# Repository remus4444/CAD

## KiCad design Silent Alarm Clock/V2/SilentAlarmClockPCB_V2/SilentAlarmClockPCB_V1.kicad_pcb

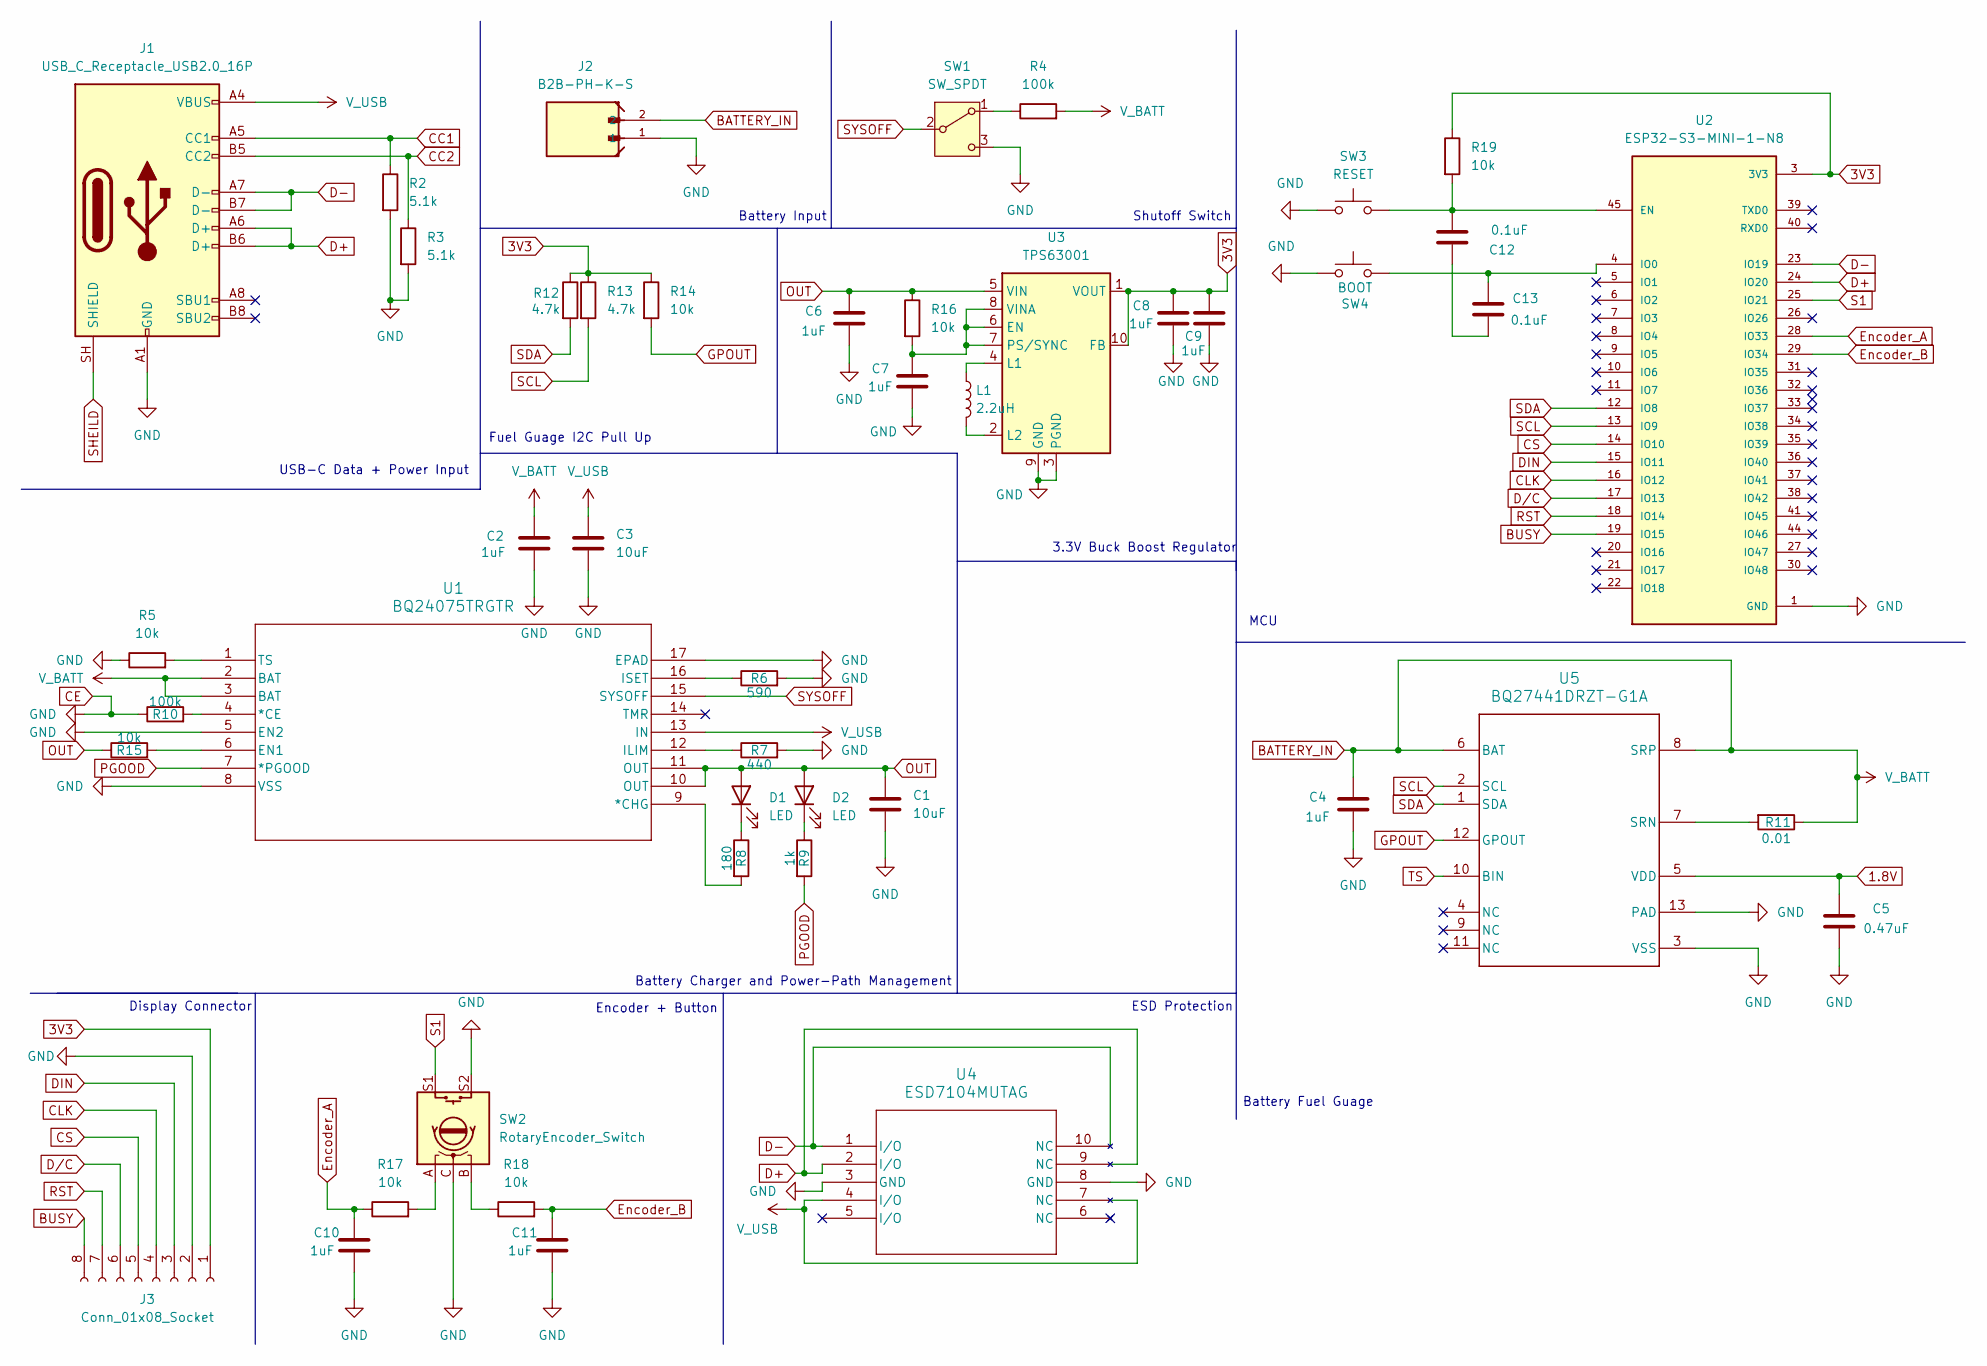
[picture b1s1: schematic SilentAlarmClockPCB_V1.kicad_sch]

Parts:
C1, C3: 10uF; C_0603_1608Metric
C2, C4, C6, C7, C8, C9, C10, C11: 1uF; C_0603_1608Metric
C5: 0.47uF; C_0603_1608Metric
C12, C13: 0.1uF; C_0603_1608Metric
D1: LED; LED_0603_1608Metric_Pad1.05x0.95mm_HandSolder
D2: LED; LED_0603_1608Metric
J1: USB_C_Receptacle_USB2.0_16P; USB_C_Receptacle_GCT_USB4105-xx-A_16P_TopMnt_Horizontal
J2: B2B-PH-K-S; JST_B2B-PH-K-S
J3: Conn_01x08_Socket; JST_PH_B8B-PH-K_1x08_P2.00mm_Vertical
L1: 2.2uH; L_1008_2520Metric
R2, R3: 5.1k; R_0603_1608Metric
R4, R10: 100k; R_0603_1608Metric
R5, R14, R15, R16, R17, R18, R19: 10k; R_0603_1608Metric
R6: 590; R_0603_1608Metric
R7: 440; R_0603_1608Metric
R8: 180; R_0603_1608Metric
R9: 1k; R_0603_1608Metric
R11: 0.01; R_0603_1608Metric
R12, R13: 4.7k; R_0603_1608Metric
SW1: SW_SPDT; SW_SPDT_CK_JS102011SAQN
SW2: RotaryEncoder_Switch; XDCR_PEC11R-4220F-S0024
SW3: RESET; SW_SPST_PTS810
SW4: BOOT; SW_SPST_PTS810
U1: BQ24075TRGTR; RGT16_1P7X1P7
U2: ESP32-S3-MINI-1-N8; XCVR_ESP32-S3-MINI-1-N8; PARTREV v0.6
U3: TPS63001; Texas_DRC0010J_ThermalVias
U4: ESD7104MUTAG; UDFN10_ONS
U5: BQ27441DRZT-G1A; Copy of DRZ0012A

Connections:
1.8V: C5.2, U5.5 (VDD)
3V3: C8.2, C9.2, J3.1, R12.1, R13.1, R14.1, R19.1, U2.3 (3V3), U3.1 (VOUT), U3.10 (FB)
BATTERY_IN: C2.1, C4.2, J2.2, R4.2, R11.1, U1.2 (BAT), U1.3 (BAT), U5.6 (BAT), U5.8 (SRP)
BUSY: J3.8, U2.19 (IO15)
CC1: J1.A5 (CC1), R2.1
CC2: J1.B5 (CC2), R3.1
CLK: J3.4, U2.16 (IO12)
CS: J3.5, U2.14 (IO10)
D+: J1.A6 (D+), J1.B6 (D+), U2.24 (IO20), U4.2 (I/O), U4.9 (NC)
D-: J1.A7 (D-), J1.B7 (D-), U2.23 (IO19), U4.1 (I/O), U4.10 (NC)
DIN: J3.3, U2.15 (IO11)
D/C: J3.6, U2.17 (IO13)
Encoder_A: C10.2, R17.1, U2.28 (IO33)
Encoder_B: C11.2, R18.2, U2.29 (IO34)
GND: C1.2, C2.2, C3.2, C4.1, C5.1, C6.1, C7.1, C8.1, C9.1, C10.1, C11.1, J1.A1 (GND), J1.A12 (GND), J1.B1 (GND), J1.B12 (GND), J2.1, J3.2, R2.2, R3.2, R5.1, R6.2, R7.2, R10.1, SW1.3 (C), SW2.C, SW2.S2, SW3.1, SW4.1, U1.5 (EN2), U1.8 (VSS), U1.17 (EPAD), U2.1 (GND), U2.2 (GND), U2.42 (GND), U2.43 (GND), U2.46 (GND), U2.47 (GND), U2.48 (GND), U2.49 (GND), U2.50 (GND), U2.51 (GND), U2.52 (GND), U2.53 (GND), U2.54 (GND), U2.55 (GND), U2.56 (GND), U2.57 (GND), U2.58 (GND), U2.59 (GND), U2.60 (GND), U2.61 (GND), U2.61_1 (GND), U2.61_2 (GND), U2.61_3 (GND), U2.61_4 (GND), U2.61_5 (GND), U2.61_6 (GND), U2.61_7 (GND), U2.61_8 (GND), U2.62 (GND), U2.63 (GND), U2.64 (GND), U2.65 (GND), U3.3 (PGND), U3.9 (GND), U3.11 (PGND), U4.3 (GND), U4.8 (GND), U5.3 (VSS), U5.13 (PAD), U5.V; also elsewhere on the board
GPOUT: R14.2, U5.12 (GPOUT)
unnamed: C12.1, C13.1
unnamed: D1.1 (K), R8.1
unnamed: D2.1 (K), R9.1
unnamed: R17.2, SW2.A
unnamed: R18.1, SW2.B
unnamed: R4.1, SW1.1 (A)
unnamed: R10.2, U1.4 (*CE)
unnamed: R8.2, U1.9 (*CHG)
unnamed: R15.2, U1.6 (EN1)
unnamed: R7.1, U1.12 (ILIM)
unnamed: R6.1, U1.16 (ISET)
unnamed: R5.2, U1.1 (TS)
unnamed 28: C12.2, R19.2, SW3.2, U2.45 (EN); also elsewhere on the board
unnamed 29: C13.2, SW4.2, U2.4 (IO0); also elsewhere on the board
unnamed: C7.2, R16.2, U3.6 (EN), U3.7 (PS/SYNC), U3.8 (VINA)
unnamed: L1.1, U3.4 (L1)
unnamed: L1.2, U3.2 (L2)
unnamed: R11.2, U5.7 (SRN)
OUT: C1.1, C6.2, D1.2 (A), D2.2 (A), R15.1, R16.1, U1.10 (OUT), U1.11 (OUT), U3.5 (VIN)
PGOOD: R9.2, U1.7 (*PGOOD)
RST: J3.7, U2.18 (IO14)
S1: SW2.S1, U2.25 (IO21)
SCL: R13.2, U2.13 (IO9), U5.2 (SCL)
SDA: R12.2, U2.12 (IO8), U5.1 (SDA)
SHEILD: J1.SH (SHIELD)
SYSOFF: SW1.2 (B), U1.15 (SYSOFF)
TS: U5.10 (BIN)
V_USB: C3.1, J1.A4 (VBUS), J1.A9 (VBUS), J1.B4 (VBUS), J1.B9 (VBUS), U1.13 (IN), U4.4 (I/O), U4.7 (NC)

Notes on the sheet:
Battery Input
MCU
Battery Fuel Guage
Battery Charger and Power-Path Management
3.3V Buck Boost Regulator
Display Connector
ESD Protection
Shutoff Switch
Fuel Guage I2C Pull Up
Encoder + Button
USB-C Data + Power Input

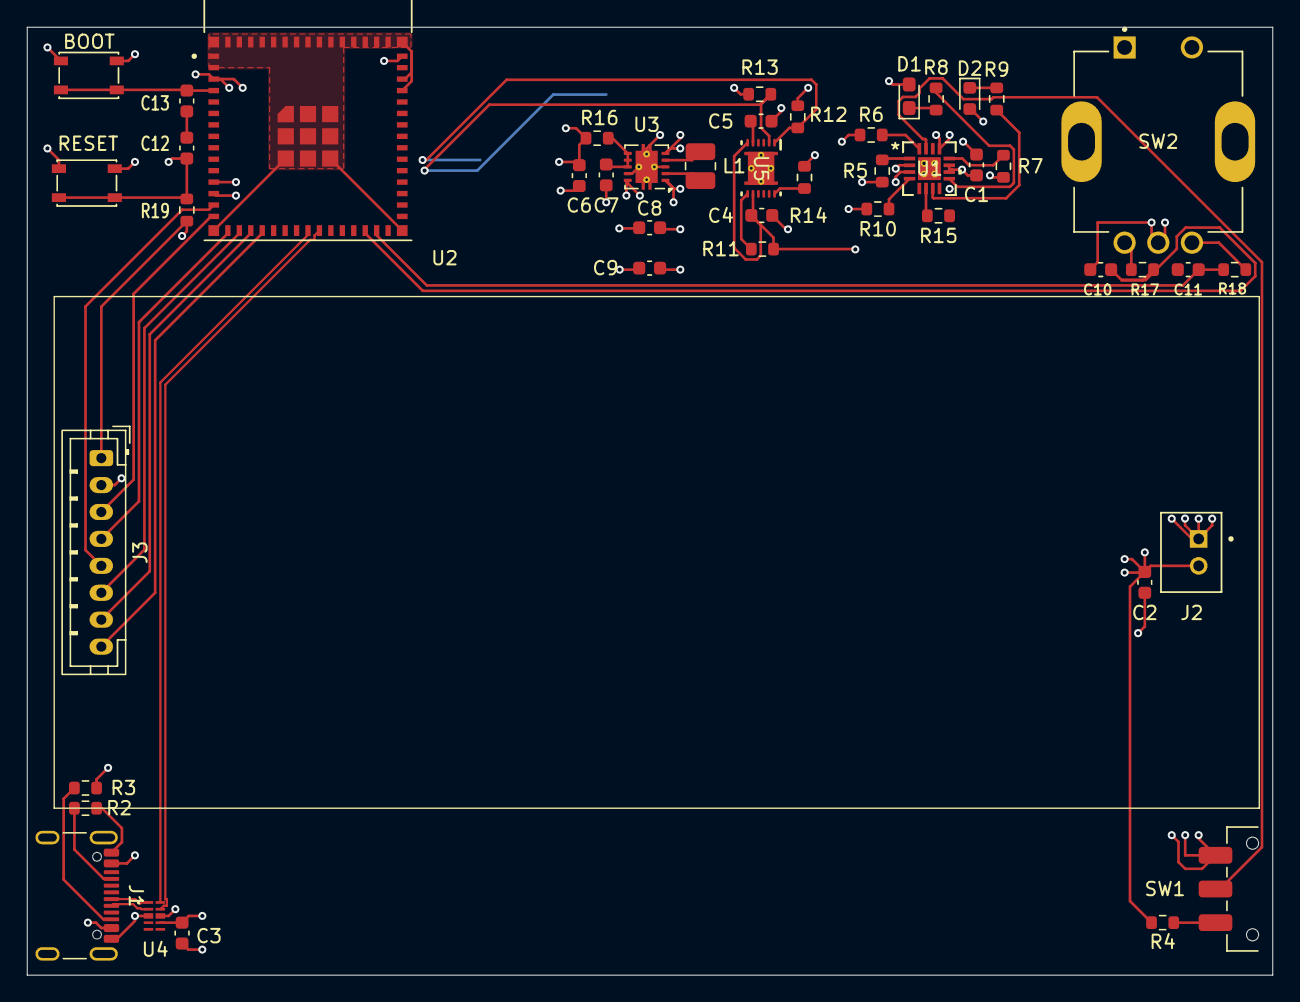
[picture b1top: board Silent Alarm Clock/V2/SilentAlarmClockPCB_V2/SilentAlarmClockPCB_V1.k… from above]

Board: 4 copper layers, 92.5 x 70.4 mm, 46 parts (0 on the bottom side), 41 nets.

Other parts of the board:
BOOT: BOOT; SW_SPST_PTS810
RESET: RESET; SW_SPST_PTS810

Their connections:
GND: BOOT.1, RESET.1; also elsewhere on the board
unnamed 28: RESET.2; also elsewhere on the board
unnamed 29: BOOT.2; also elsewhere on the board

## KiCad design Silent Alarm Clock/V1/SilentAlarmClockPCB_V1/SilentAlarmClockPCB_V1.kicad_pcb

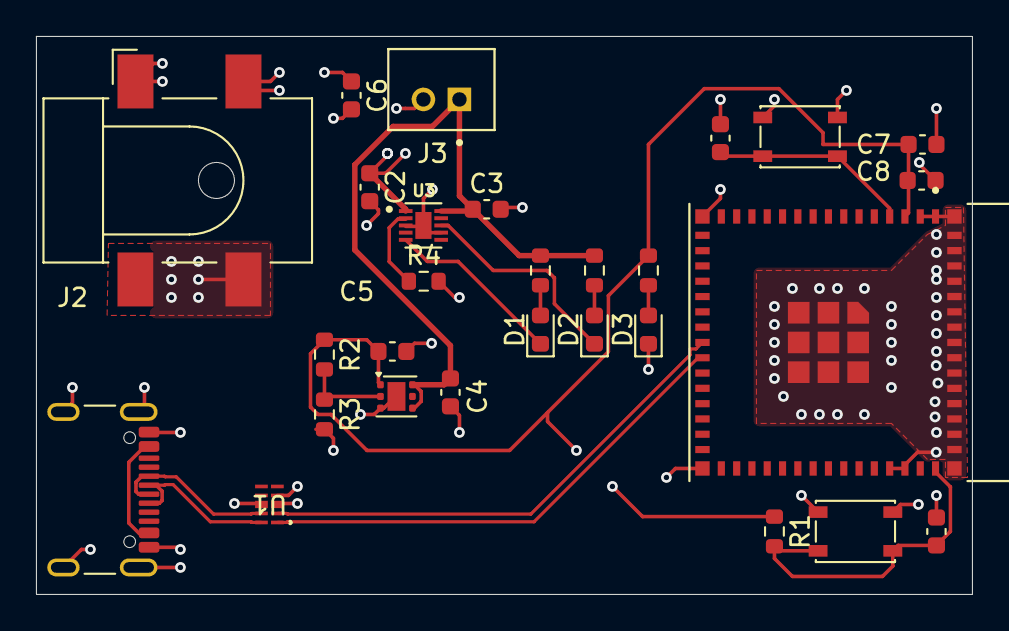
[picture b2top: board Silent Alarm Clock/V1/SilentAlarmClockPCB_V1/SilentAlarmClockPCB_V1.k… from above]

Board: 4 copper layers, 52.0 x 31.0 mm, 28 parts (0 on the bottom side), 16 nets.

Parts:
C2, C3, C4, C5: 1uF; C_0603_1608Metric
C6, C7, C8: C; C_0603_1608Metric
C9, C10: 0.1uF; C_0603_1608Metric
D1, D2, D3: LED; LED_0603_1608Metric
J1: USB_C_Receptacle_USB2.0_16P; USB_C_Receptacle_GCT_USB4105-xx-A_16P_TopMnt_Horizontal
J2: Barrel_Jack; BarrelJack_CLIFF_FC681465S_SMT_Horizontal
J3: B2B-PH-K-S; JST_B2B-PH-K-S
R1, R5, R6, R7: 1k; R_0603_1608Metric
R2, R3: R; R_0603_1608Metric
R4: 540; R_0603_1608Metric
SW3: RESET; SW_SPST_PTS810
SW4: BOOT; SW_SPST_PTS810
U1: ESD7104MUTAG; UDFN10_ONS
U2: ESP32-S3-MINI-1-N8; XCVR_ESP32-S3-MINI-1-N8
U3: BQ24040DSQR; SON40P200X200X80-11N
U4: TLV75801PDRV; WSON-6-1EP_2x2mm_P0.65mm_EP1x1.6mm

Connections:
/3V3: C5.1, C7.1, C8.1, R1.1, R2.1, R7.1, U2.3 (3V3), U4.1 (OUT)
/5VIN: C2.1, C6.1, J2.1, U1.4 (I/O), U3.1 (IN)
/USB_N: J1.A7 (D-), J1.B7 (D-), U1.2 (I/O), U2.23 (IO19)
/USB_P: J1.A6 (D+), J1.B6 (D+), U1.1 (I/O), U2.24 (IO20)
GND: C2.2, C3.2, C4.2, C5.2, C6.2, C7.2, C8.2, C9.2, C10.2, D3.1 (K), J1.A1 (GND), J1.A12 (GND), J1.B1 (GND), J1.B12 (GND), J1.SH (SHIELD), J2.2, J3.2, R3.2, R4.2, SW3.1, SW4.1, U1.3 (GND), U1.8 (GND), U2.1 (GND), U2.2 (GND), U2.42 (GND), U2.43 (GND), U2.46 (GND), U2.47 (GND), U2.48 (GND), U2.49 (GND), U2.50 (GND), U2.51 (GND), U2.52 (GND), U2.53 (GND), U2.54 (GND), U2.55 (GND), U2.56 (GND), U2.57 (GND), U2.58 (GND), U2.59 (GND), U2.60 (GND), U2.61 (GND), U2.61_1 (GND), U2.61_2 (GND), U2.61_3 (GND), U2.61_4 (GND), U2.61_5 (GND), U2.61_6 (GND), U2.61_7 (GND), U2.61_8 (GND), U2.62 (GND), U2.63 (GND), U2.64 (GND), U2.65 (GND), U3.3 (VSS), U3.7 (ISET2), U3.11 (EXP), U4.3 (GND), U4.7 (GND)
unnamed: D1.2 (A), R5.2
unnamed: D1.1 (K), U3.5 (~PG)
unnamed: D2.2 (A), R6.2
unnamed: D2.1 (K), U3.8 (~CHG)
unnamed: D3.2 (A), R7.2
unnamed: J1.A4 (VBUS), J1.A9 (VBUS), J1.B4 (VBUS), J1.B9 (VBUS)
unnamed: C9.1, R1.2, SW3.2, U2.45 (EN)
unnamed: C10.1, SW4.2, U2.4 (IO0)
unnamed: R4.1, U3.2 (ISET)
unnamed: C3.1, C4.1, J3.1, R5.1, R6.1, U3.10 (OUT), U4.4 (EN), U4.6 (IN)
unnamed: R2.2, R3.1, U4.2 (FB)

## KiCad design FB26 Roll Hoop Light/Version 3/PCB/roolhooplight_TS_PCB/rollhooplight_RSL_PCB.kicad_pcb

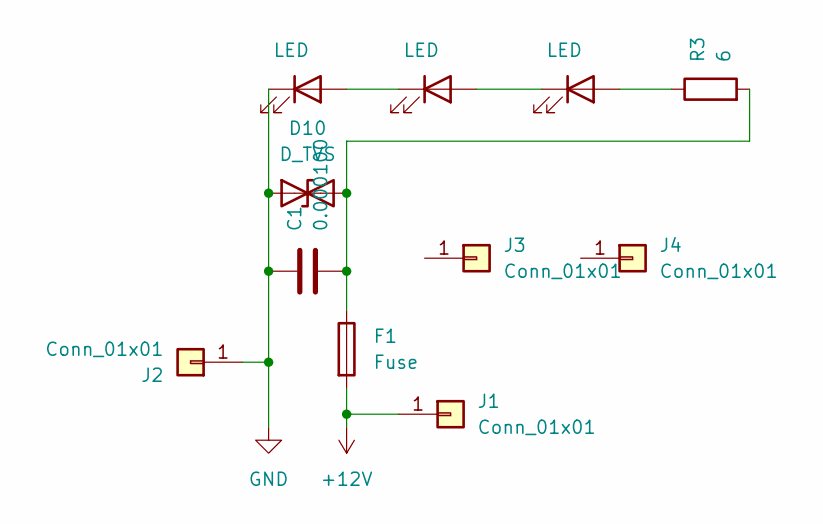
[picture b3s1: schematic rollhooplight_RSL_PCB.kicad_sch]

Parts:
C1: 0.000100; C_1206_3216Metric
D3, D6, D9: LED; LED_Cree-XP
D10: D_TVS; D_SMB
F1: Fuse; Fuse_1206_3216Metric
J1, J2: Conn_01x01; MountingHole_2.2mm_M2_Pad
J3, J4: Conn_01x01; MountingHole_2.2mm_M2
R3: 6; RES_35606R2FT

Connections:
+12V: F1.2, J1.1 (Pin_1_1)
GND: C1.1, D3.1 (K), D3.3, D6.3, D9.3, D10.1 (A1), J2.1 (Pin_1_1)
unnamed: D3.2 (A), D6.1 (K)
unnamed: D6.2 (A), D9.1 (K)
unnamed: D9.2 (A), R3.1
unnamed: C1.2, D10.2 (A2), F1.1, R3.2

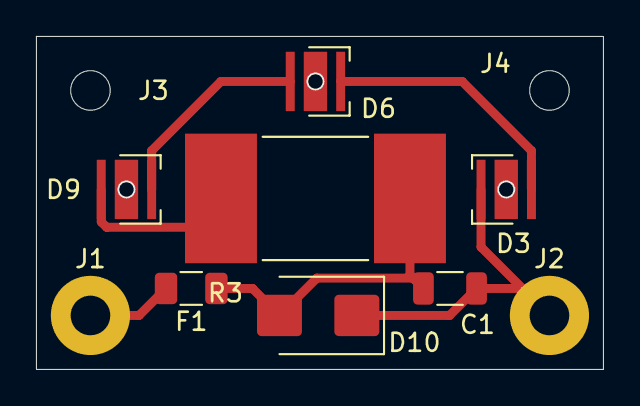
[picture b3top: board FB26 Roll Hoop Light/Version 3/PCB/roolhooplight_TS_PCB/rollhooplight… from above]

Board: 2 copper layers, 31.5 x 18.5 mm, 11 parts (0 on the bottom side), 6 nets.

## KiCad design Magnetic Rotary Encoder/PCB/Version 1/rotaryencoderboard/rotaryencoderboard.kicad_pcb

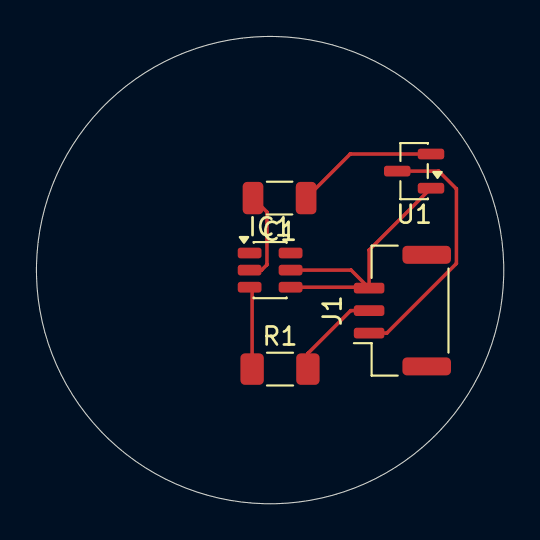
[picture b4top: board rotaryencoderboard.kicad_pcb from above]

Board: 2 copper layers, 26.0 x 26.0 mm, 5 parts (0 on the bottom side), 6 nets.

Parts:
C1: 100*10^-9; C_1206_3216Metric
IC1: AS5600-ASOT; SOT-23-6
J1: Conn_01x03_Pin; JST_GH_SM03B-GHS-TB_1x03-1MP_P1.25mm_Horizontal
R1: 10000; R_1206_3216Metric_Pad1.30x1.75mm_HandSolder
U1: MCP1700x-330xxTT; SOT-23

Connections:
3.3V: C1.2, IC1.2 (VDD3V3)
5V: J1.1, U1.3 (VI)
GND: IC1.4 (GND), IC1.5 (PGO), J1.3, U1.1 (GND)
unnamed: IC1.3 (OUT), R1.1
unnamed: C1.1, U1.2 (VO)
OUT: J1.2, R1.2

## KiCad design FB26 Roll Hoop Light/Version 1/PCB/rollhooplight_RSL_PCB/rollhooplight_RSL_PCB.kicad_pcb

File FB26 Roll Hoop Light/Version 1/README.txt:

Version 1 turned on sucessfully however it over heated within 15 seconds of operations, making a puff of smoke.

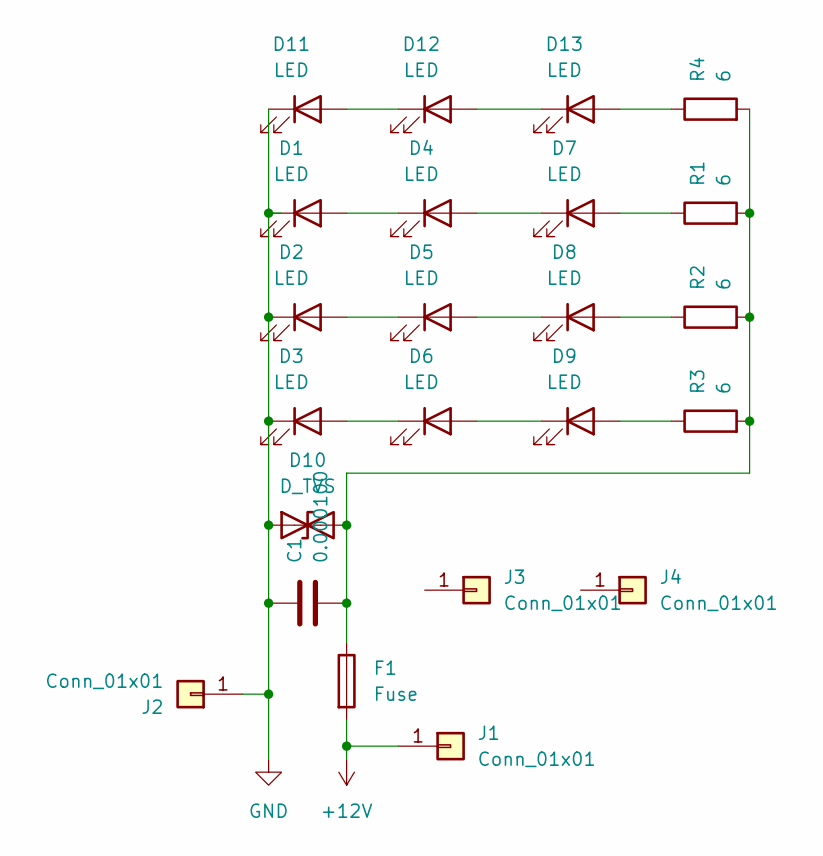
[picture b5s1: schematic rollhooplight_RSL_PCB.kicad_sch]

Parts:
C1: 0.000100; C_1206_3216Metric
D1, D2, D3, D4, D5, D6, D7, D8, D9, D11, D12, D13: LED; LED_SST-10-G-B130_LMD
D10: D_TVS; D_SMB
F1: Fuse; Fuse_1206_3216Metric
J1, J2: Conn_01x01; MountingHole_2.2mm_M2_Pad
J3, J4: Conn_01x01; MountingHole_2.2mm_M2
R1, R2, R3, R4: 6; R_2512_6332Metric

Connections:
+12V: F1.2, J1.1
GND: C1.1, D1.1 (K), D2.1 (K), D3.1 (K), D10.1 (A1), D11.1 (K), J2.1
unnamed: D1.2 (A), D4.1 (K)
unnamed: D2.2 (A), D5.1 (K)
unnamed: D3.2 (A), D6.1 (K)
unnamed: D4.2 (A), D7.1 (K)
unnamed: D5.2 (A), D8.1 (K)
unnamed: D6.2 (A), D9.1 (K)
unnamed: D7.2 (A), R1.1
unnamed: D8.2 (A), R2.1
unnamed: D9.2 (A), R3.1
unnamed: C1.2, D10.2 (A2), F1.1, R1.2, R2.2, R3.2, R4.2
unnamed: D11.2 (A), D12.1 (K)
unnamed: D12.2 (A), D13.1 (K)
unnamed: D13.2 (A), R4.1

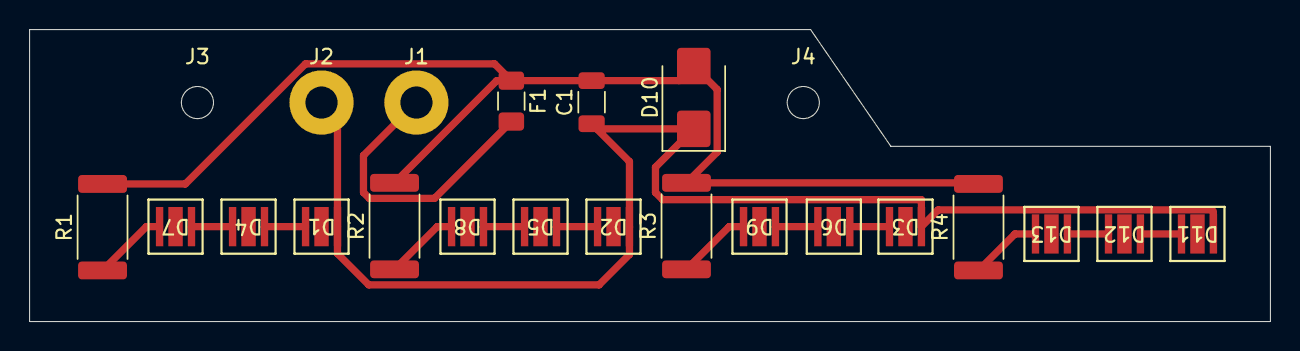
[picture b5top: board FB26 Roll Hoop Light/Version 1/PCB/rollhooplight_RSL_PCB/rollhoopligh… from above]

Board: 2 copper layers, 85.0 x 20.0 mm, 23 parts (0 on the bottom side), 15 nets.

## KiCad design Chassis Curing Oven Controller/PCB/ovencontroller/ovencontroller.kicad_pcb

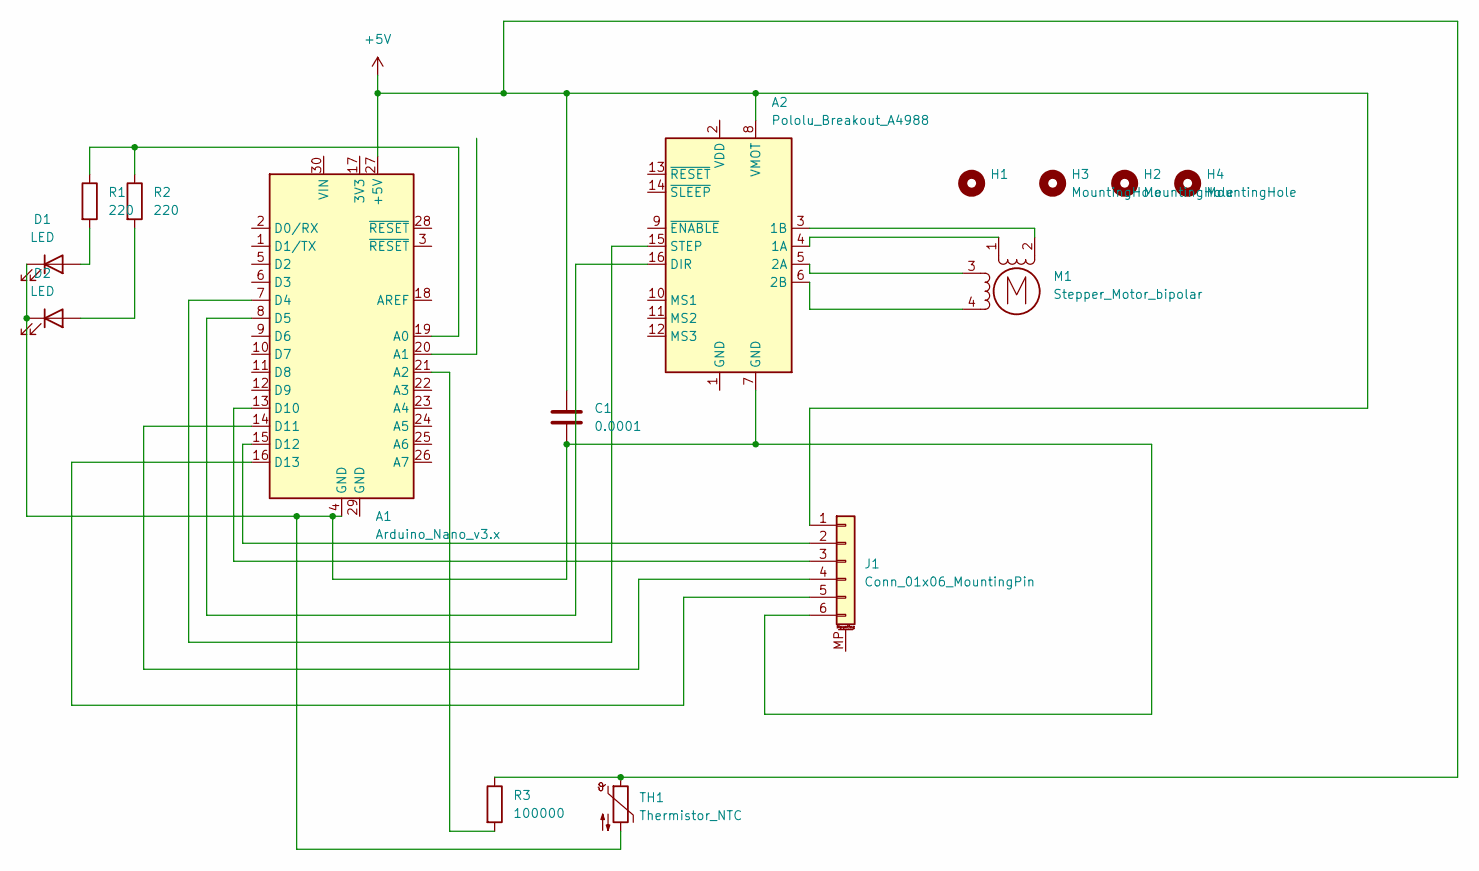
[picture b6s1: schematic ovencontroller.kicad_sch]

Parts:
A1: Arduino_Nano_v3.x; Arduino_Nano
A2: Pololu_Breakout_A4988; Pololu_Breakout-16_15.2x20.3mm
C1: 0.0001; C_Disc_D5.0mm_W2.5mm_P2.50mm
D1, D2: LED; LED_D3.0mm
H1, H2, H3, H4: MountingHole; MountingHole_3.2mm_M3
J1: Conn_01x06_MountingPin; revpinout
M1: Stepper_Motor_bipolar; motorconnector
R1, R2: 220; R_Axial_DIN0207_L6.3mm_D2.5mm_P7.62mm_Horizontal
R3: 100000; R_Axial_DIN0207_L6.3mm_D2.5mm_P7.62mm_Horizontal
TH1: Thermistor_NTC; JST_EH_B2B-EH-A_1x02_P2.50mm_Vertical

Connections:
+5V: A1.27 (+5V), A2.8 (VMOT), C1.1, J1.1, R3.1, TH1.1
unnamed: A1.19 (A0), R1.1, R2.1
unnamed: A1.21 (A2), R3.2
unnamed: A1.7 (D4), A2.15 (STEP)
unnamed: A1.8 (D5), A2.16 (DIR)
unnamed: A1.13 (D10), J1.3
unnamed: A1.14 (D11), J1.4
unnamed: A1.15 (D12), J1.2
unnamed: A1.16 (D13), J1.5
unnamed: A2.4 (1A), M1.1
unnamed: A2.3 (1B), M1.2 (-)
unnamed: A2.5 (2A), M1.3
unnamed: A2.6 (2B), M1.4
unnamed: D1.2 (A), R1.2
unnamed: A1.4 (GND), A2.7 (GND), C1.2, D1.1 (K), D2.1 (K), J1.6, TH1.2
unnamed: D2.2 (A), R2.2

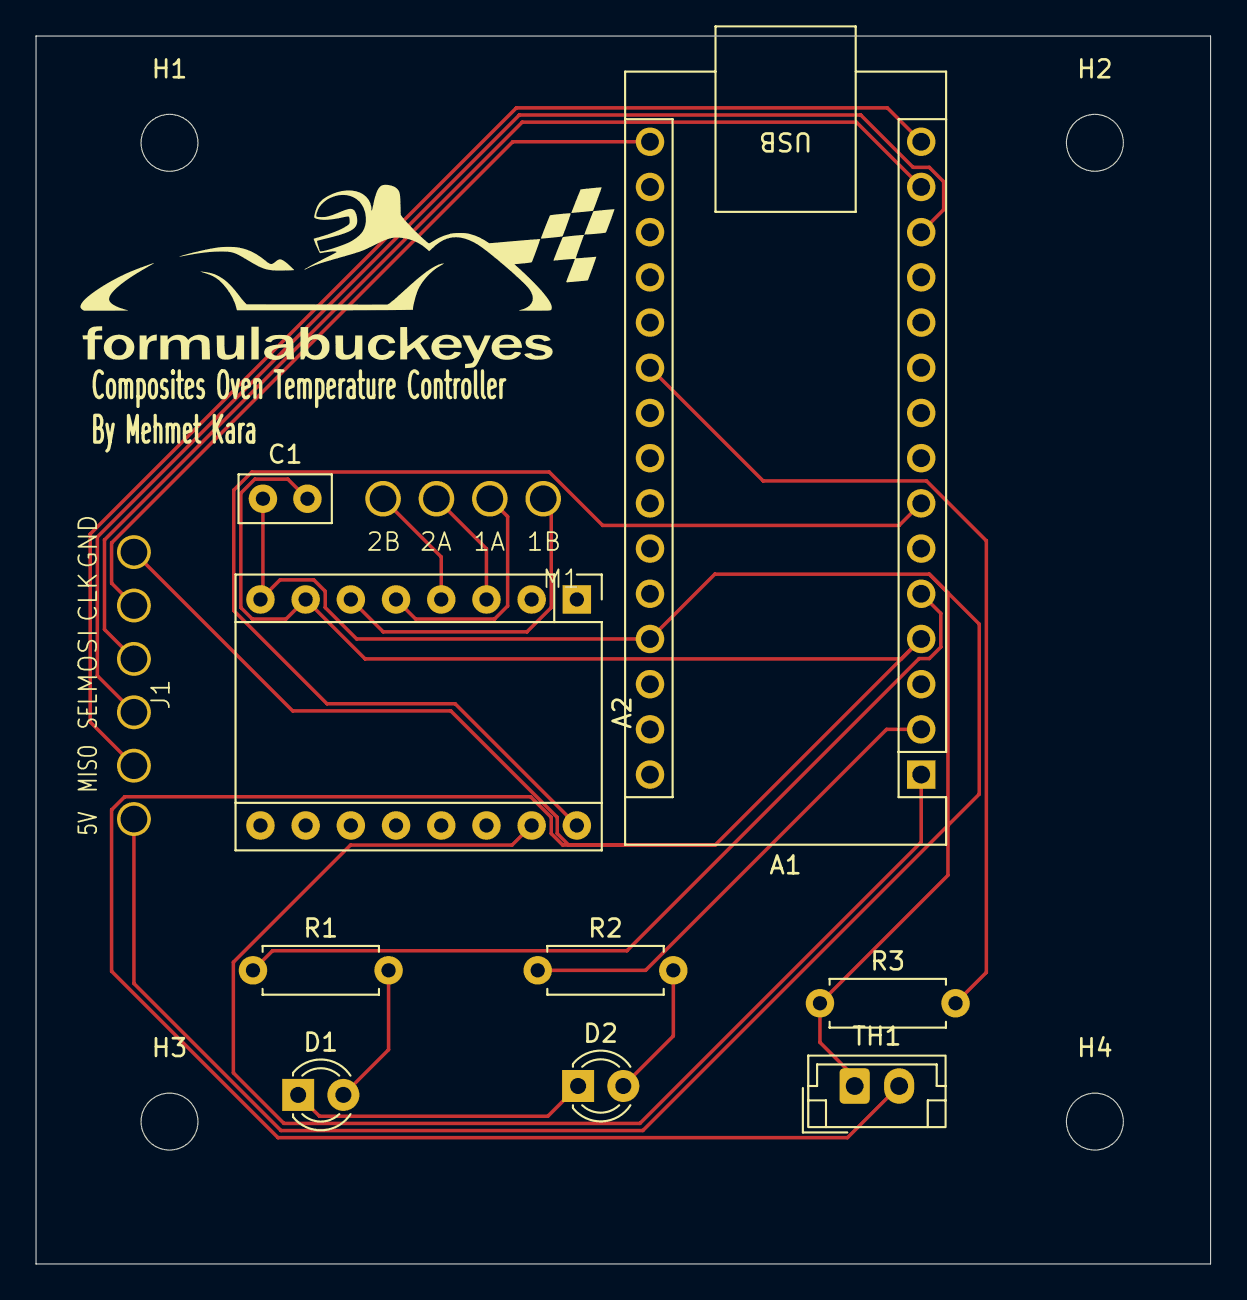
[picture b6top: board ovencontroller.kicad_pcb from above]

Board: 2 copper layers, 66.0 x 69.0 mm, 15 parts (0 on the bottom side), 16 nets.

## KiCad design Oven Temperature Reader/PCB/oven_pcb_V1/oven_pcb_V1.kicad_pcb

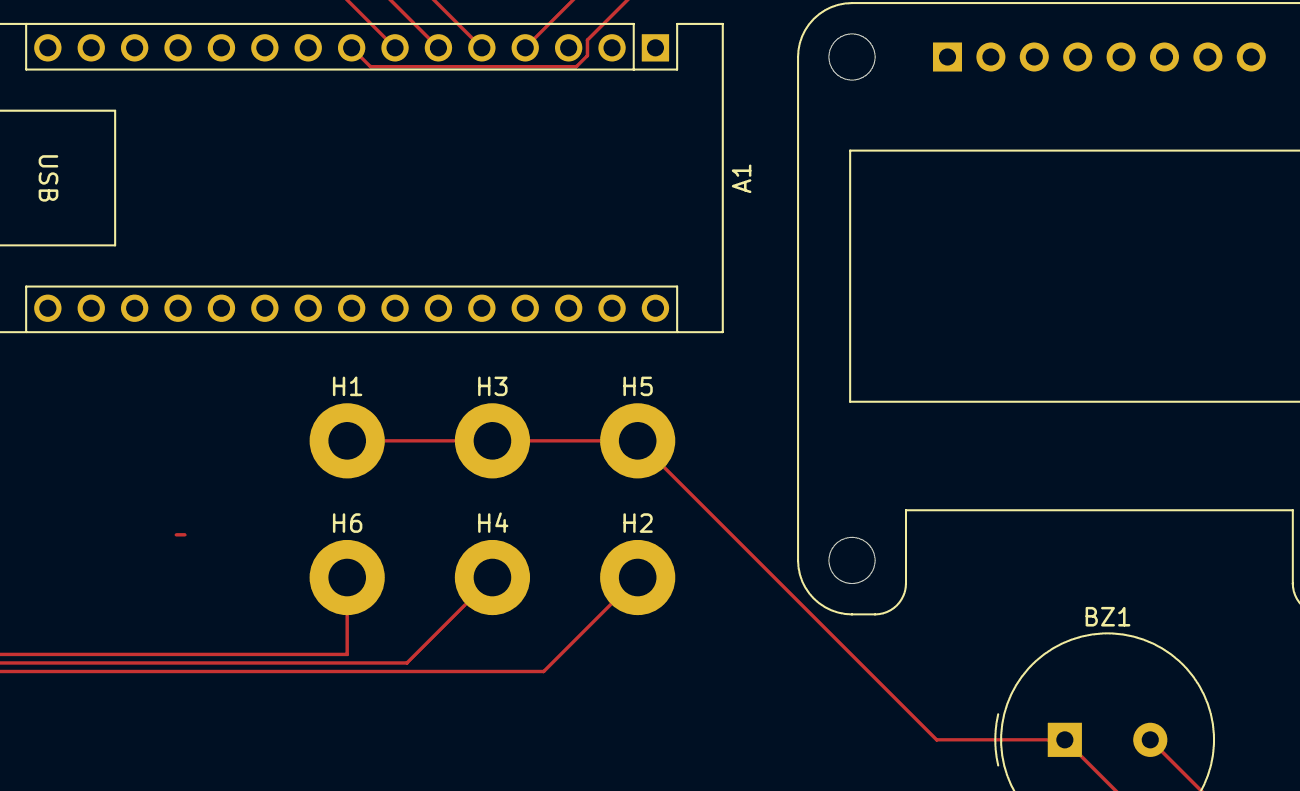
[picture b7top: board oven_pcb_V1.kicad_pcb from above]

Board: 2 copper layers, 13 parts (0 on the bottom side), 5 nets.

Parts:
A1: Arduino_Nano_v3.x; Arduino_Nano
BZ1: Buzzer; Buzzer_TDK_PS1240P02BT_D12.2mm_H6.5mm
H1, H2, H3, H4, H5, H6: MountingHole_Pad; MountingHole_2.2mm_M2_Pad
H7, H8, H9, H10: MountingHole; MountingHole_4.3mm_M4
U1: SSD1306; Adafruit_SSD1306

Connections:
GND: A1.4 (GND), BZ1.1 (+), H1.1, H3.1, H5.1
unnamed: A1.5 (D2), H2.1
unnamed: A1.6 (D3), H4.1
unnamed: A1.7 (D4), H6.1
unnamed: A1.8 (D5), BZ1.2 (-)

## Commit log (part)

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2026-01-08 Created pill container CAD
2026-01-09 updated pill container and added utensil tray
2026-01-26 Shortened threads for pill container
2026-02-07 Medium sized utensile tray bit uploaded
2026-02-07 Oven temperature reader project started
    A device to read the temperature of demi's oven
2026-02-11 Started work on the oven temp guage
2026-02-20 Work in progress composites oven controller first push
2026-02-23 changes to curing controller
2026-02-23 Griffins NVME m.2 SSD holder
2026-02-26 Started the Formula Buckeyes Voron project
2026-02-26 changes to oven temp controller
2026-03-21 original firmware file backup
2026-04-05 Measurements project first push
2026-04-05 Misc voron updates
2026-04-08 Added voron components documentation
2026-05-01 Ultrasonic sensor calib update
2026-05-01 voron update
2026-05-01 oven reader update
2026-05-01 chassis oven curing update
2026-05-01 Roll hoop light PCB initial push
2026-05-08 Added Solar Car load casing script
2026-05-10 Version 2 boards
2026-05-10 Rotary encoder PCB first iteration
2026-05-24 Version 3 tractive light
